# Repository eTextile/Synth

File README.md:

# eTextile-Synthesizer
### Exploring music through textile

## About the project
**eTextile-Synthesizers** are handcrafted multi-touch digital interfaces based on smart textile materials and custom electronic solutions. The project features a fully embedded multitouch controller that combines the powerful **Teensy 4.0** MCU with the **E256 eTextile matrix sensor** — a 16×16 FSR array with hardware interpolation up to 64×64 points.

The interface is configured via a **browser-based mapping application** that communicates with the device over USB-MIDI. Mappings (touchpad, slider, switch, knob, grid…) are defined visually, saved as JSON, and uploaded to the device.

### Links
* **Web page:** [synth.eTextile.org](https://synth.eTextile.org "Project web page")
* **Mapping app:** [github.com/eTextile/Mapping](https://github.com/eTextile/Mapping "Browser-based MIDI mapping application")
* **Repository:** [github.com/eTextile/Synth](https://github.com/eTextile/Synth "Project repository")
* **License:** [CC-BY-SA](https://github.com/eTextile/Synth/blob/master/LICENSE.txt "Project License")
* **Mail:** [contact@etextile.org](mailto:contact@etextile.org "eMail us")
* **Pictures:** [flickr.com](https://www.flickr.com/photos/maurin/albums/72157673740361510/ "Share your pictures with us")

## Project content
* **Hardware_textile:** eTextile-Synthesizer construction tutorial
* **Hardware_electronic:** Open Hardware electronics (KiCad)
* **Firmware:** eTextile-Synthesizer firmware (PlatformIO)
* **Software:** Demo applications (PureData, MaxMSP, Max4Live, etc.)

## Specifications
| **Feature**              | **Description**                            |
| :----------------------- | :----------------------------------------- |
| Power                    | DC 5V (USB)                                |
| Sensor resolution        | 16×16 FSRs                                 |
| Interpolated resolution  | 64×64                                      |
| Multi-touch              | User defined                               |
| Blob characteristics     | [ID, STATE, CX, CY, WIDTH, HEIGHT, DEPTH]  |
| XY resolution            | [0:127] integer                            |
| Z resolution             | [0:127] integer                            |
| FPS                      | 500–550                                    |
| Audio IN                 | ADC 16-bit (mini-jack)                     |
| Audio OUT 1              | DAC 16-bit (mini-jack)                     |
| Audio OUT 2              | Headphone (mini-jack)                      |
| Connectivity             | USB-MIDI                                   |
| Connectivity             | MIDI I/O (mini-jack)                       |
| Connectivity             | USB-MPE (TODO)                             |

## Publications
- [NIME17](http://www.nime2017.org/) - Designing a Multi-Touch eTextile for Music Performances / [Paper](https://github.com/eTextile/Matrix/blob/teensy_matrix/docs/publications/NIME17-eTextile.pdf) - [Video](https://vimeo.com/217690743)
- [MOCO17](http://moco17.movementcomputing.org/) - Music Skin: Fabric Interface for Expressive Music Control / [Paper](https://github.com/eTextile/Matrix/blob/teensy_matrix/docs/publications/MOCO17-MusicSkin.pdf)

## Copyright
Except as otherwise noted, all files in the **eTextile-Synthesizer** project folder

    Copyright (c) 2014- Maurin Donneaud

For information on usage and redistribution, and for a DISCLAIMER OF ALL WARRANTIES, see LICENSE.txt included in this folder.

## Docs
- [Video made at Schmiede 2014](http://www.kobakant.at/DIY/?p=4305/)

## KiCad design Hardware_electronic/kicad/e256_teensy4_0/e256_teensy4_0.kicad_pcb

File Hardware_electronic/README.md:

# eTextile-Synthesizer
## Exploring music through textile

### HARDWARE_ELECTRONIC

#### PCB_SCHEMATICS
Here is the last PCB schematics document : [eTextile_synth_schematics.pdf](./docs/eTextile_synth_schematics.pdf)

#### FEATURES
- Teensy 4.0 (600MHz MCU)
- eTextile-Synthesizer PCB made with **KiCad** (V5.0.*)
- Daisy chainable design using **3.5 stereo mini Jack**
    - **LINE-OUT** : High quality 16 bit DAC OUTPUT (Headphones)
    - **SIG-IN** : Audio stereo input sampling rate 44.1 kHz
    - **SIG-OUT** : High quality 16 bit DAC OUTPUT (Line)
    - **MIDI-IN** : MIDI INPUT using mini jack 
    - **MIDI-OUT** : MIDI OUTPUT using mini jack

#### BUILT_IN SWITCHES
- **Button D1 (DOT)** Short press : CALIBRATE THE SENSOR MATRIX
- **Button D1 (DOT)** Long press : SAVE CONFIG TO FLASH MEMORY (standalone mode)
- **Button D2 (STAR)** Short press : SELECT MODE (see below)
- **Button D2 (STAR)** Long press : MIDI LEARN MODE

#### SELECT MODE
    |      MODE     |       LEDs      |                     FONCTION                    |
    | :------------ | :-------------  | :---------------------------------------------- |
    | **LINE_OUT**  | D1-OFF / D2-OFF | line_out level adjustment using rotary encoder  |
    | **SIG_IN**    | D1-ON  / D2-OFF | sig_in level adjustment using rotary encoder    |
    | **SIG_OUT**   | D1-OFF / D2-ON  | sig_out level adjustment using rotary encoder   |
    | **THRESHOLD** | D1-ON  / D2-ON  | threshold value adjustment using rotary encoder |

#### MIDI LEARN
> **TODO** — not yet implemented (long press STAR is reserved for this feature).

In MIDI LEARN mode the device will send each blob parameter (X, Y, Z, width, height) one at a time so that external software can map them without ambiguity.
Use the rotary encoder to cycle through the available parameters; the currently selected parameter is the only one transmitted.
A short press on the **DOT** or **STAR** button exits MIDI LEARN mode and returns to the previous operating mode.

> **Note:** static MIDI mappings are configured via the [Mapping web app](https://etextile.github.io/Mapping/) and uploaded to the device over USB.

#### MIDI PLUG
**MIDI TRS-A (MIDI 2.0 Standard)**

#### KICAD (Prerequisite)
- Installing KiCad : https://kicad-pcb.org/
- Installing Github Libraries : https://github.com/KiCad/
```
    mkdir KiCad_Libraries
    cd KiCad_Libraries
    git clone https://github.com/KiCad/kicad-symbols
    git clone https://github.com/KiCad/kicad-footprints
    git clone https://github.com/KiCad/kicad-packages3D
```
- Configuring KiCad Libraries
```
    KiCad > Préférences > Configure path
    KICAD_SYMBOL_DIR : (add your own path) .../KiCad_Libraries/kicad-symbols
    KICAD_TEMPLATE_DIR : DO NOT CHANGE
    KICAD_USER_TEMPLATE_DIR : DO NOT CHANGE
    KIGITHUB : DO NOT CHANGE
    KISYS3DMOD : (add your own path) .../KiCad_Libraries/kicad-packages3D
    KISYSMOD : (add your own path) .../KiCad_Libraries/kicad-footprints
```
##### PCB specifications
- **Base Material** : FR-4 TG130
- **No. of Layers** : 2 layers
- **PCB Dimensions** : 70mm / 76mm
- **No. of Different Designs** : 1
- **PCB Thickness** : 1.20 mm
- **PCB Color** : Matte Black
- **Surface Finish** : ENIG
- **Minimum Solder Mask Dam** : 0.4mm
- **Copper Weight** : 1oz.
- **Minimum Drill Hole Size** : 0.3mm
- **Trace Width / Spacing** : 6/6 mil
- **Plated Half-holes / Castellated Holes** : No
- **Impedance Control** : No

##### BOM (Bill Of Materials)
```
    matrix/Hardware_electronic/kicad/e256_teensy4_0/pick_and_place/BOM_e256_teensy4_0.xls
    matrix/Hardware_electronic/kicad/e256_teensy4_0/pick_and_place/BOM_e256_teensy4_0.cvs
```

## Acknowledgements
-  Matt Venn : for his [teensy 4.0 Open-Hardware sound_card](https://github.com/mattvenn/teensy-audio-fx) made with KiCad ;-)

## TODO
- R10 470Ω → 2.2kΩ
- R15 → 4.7 kΩ
- Add hardware MIDI THRU
- Make eTextile-Synthesizer/Dasy PCB

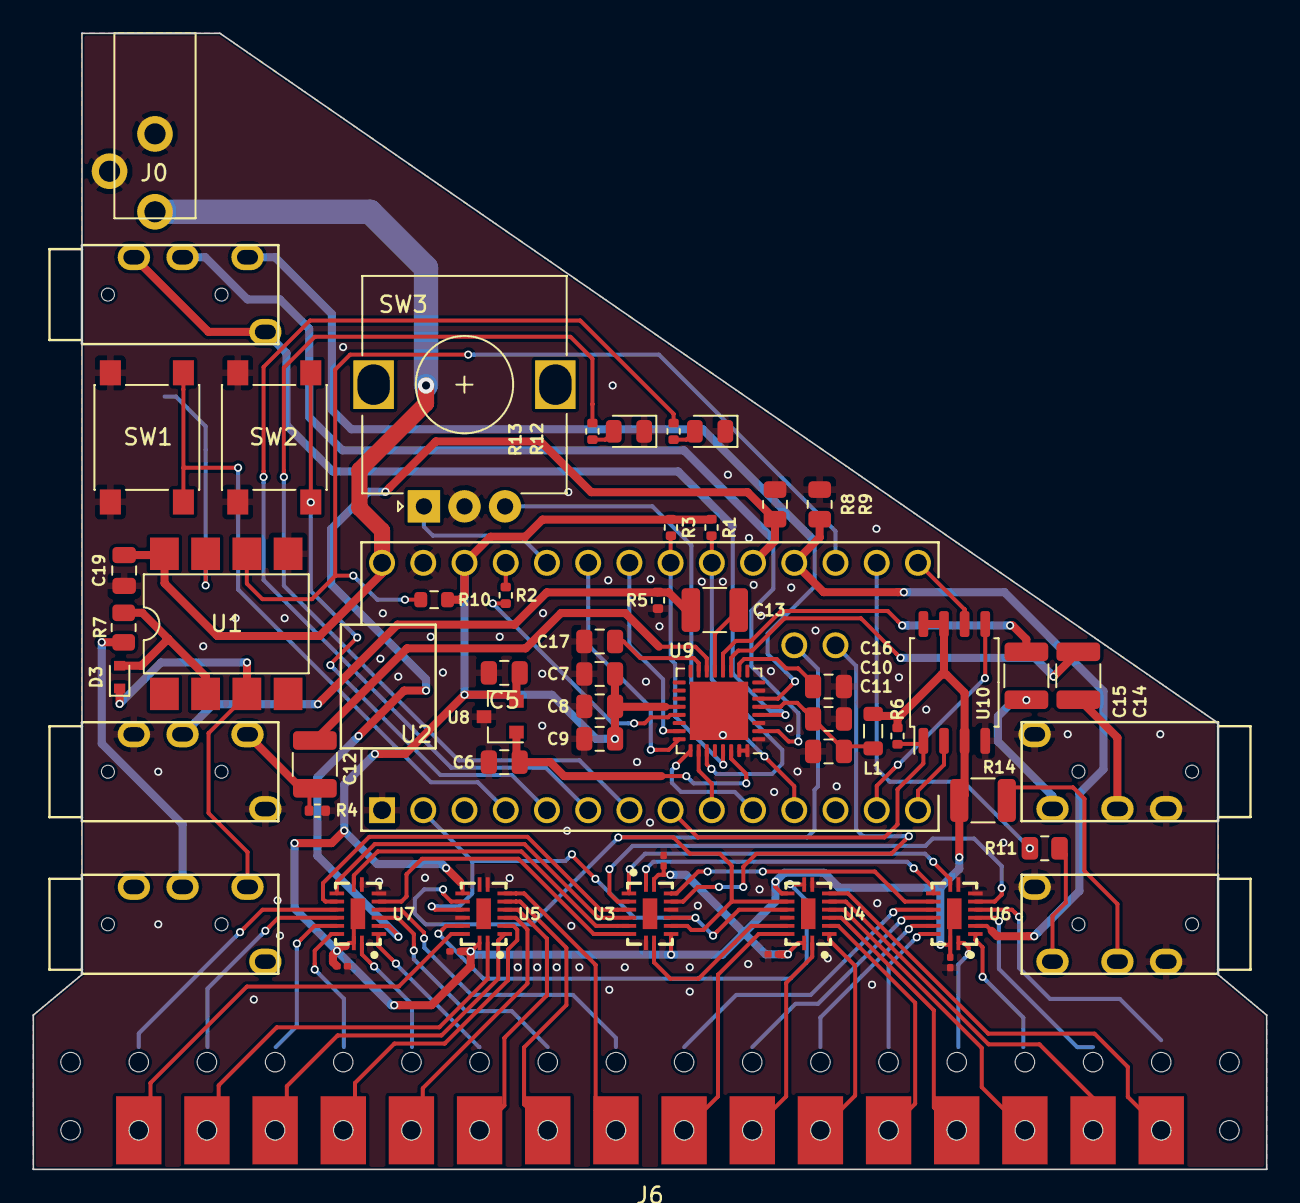
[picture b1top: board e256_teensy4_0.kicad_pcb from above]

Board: 2 copper layers, 76.0 x 70.0 mm, 58 parts (1 on the bottom side), 93 nets.

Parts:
C1, C2, C3, C4, C18: 0.1uF 6.3V X5R; C_0201_0603Metric
C5, C6: 2.2uF_X7R; C_0805_2012Metric
C7, C10: 2.2uF; C_0805_2012Metric
C8, C9, C11, C16, C17, C19: 0.1uF; C_0805_2012Metric
C12, C13, C14, C15: 1uF; C_1210_3225Metric
D1, D2: LED; LED_0805_2012Metric
D3: 1N4148; D_SOD-523
J0: Conn_Coaxial_Power; BarrelJack-SMT-DC003_Horizontal
J1: MIDI_IN; PJ-320A
J2: MIDI_OUT; PJ-320A
J3: AUDIO_IN; PJ-320A
J4: AUDIO_OUT; PJ-320A
J5: LINE_OUT; PJ-320A
J6: e256_pad_16x16; e256_pad_16X16
L1: 600R; L_0805_2012Metric
R1, R3: 2.2K; R_0402_1005Metric
R2: 100R; R_0402_1005Metric
R4, R5: 100k; R_0402_1005Metric
R6: 10K; R_0402_1005Metric
R7: 220 Ohm; R_0805_2012Metric
R8, R9: 10K; R_0805_2012Metric
R10: 470 Ohm; R_0603_1608Metric
R11: 47 Ohm 1/8W; R_0805_2012Metric
R12, R13: 100 Ohm; R_0402_1005Metric
R14: 47 Ohm 1/3W; R_1210_3225Metric
R15: 10K; R_0805_2012Metric_Pad1.20x1.40mm_HandSolder
SW1, SW2: SW_Push; SW_SPST_PTS645
SW3: RotaryEncoder_Switch; RotaryEncoder_Alps_EC12E_Vertical_H20mm
U1: 6N138SM; 6N138SM_8-SMD
U2: Teensy4.0; Teensy40
U3, U4, U5: 74HC595BQ; DHVQFN-16-2.5X3.5MM
U6, U7: 74HC4051BQ; DHVQFN-16-2.5X3.5MM
U8: MCP1811A; SOT-23
U9: SGTL5000; QFN-32-1EP_5x5mm_P0.5mm_EP3.6x3.6mm
U10: W25Q128JVS; SOIC-8_5.23x5.23mm_P1.27mm

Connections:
+1V8: C6.1, U8.1, U9.30
+5V: C19.1, J0.1, U1.8, U2.33
/SGTL5000/filter_audio_3v3: C10.1, C11.1, L1.2, U9.5
ANALOG_0: R9.1, U2.23, U6.3
ANALOG_1: R8.1, U2.24, U7.3
BCLK: U2.28, U9.24
COL_0: J6.16, U4.7
COL_1: J6.17, U4.6
COL_2: J6.18, U4.5
COL_3: J6.19, U4.4
COL_4: J6.20, U4.3
COL_5: J6.21, U4.2
COL_6: J6.22, U4.1
COL_7: J6.23, U4.15
COL_8: J6.24, U5.7
COL_9: J6.25, U5.6
COL_10: J6.26, U5.5
COL_11: J6.27, U5.4
COL_12: J6.28, U5.3
COL_13: J6.29, U5.2
COL_14: J6.30, U5.1
COL_15: J6.31, U5.15
DS_B: U3.9, U4.14
DS_C: U4.9, U5.14
ENCODER_A: SW3.A, U2.29
ENCODER_B: SW3.B, U2.11
EN_A: U3.3, U6.6
EN_B: U3.7, U7.6
GND: C1.2, C2.2, C3.2, C4.2, C5.2, C6.2, C7.2, C8.2, C9.2, C10.2, C11.2, C16.2, C17.2, C18.2, C19.2, D1.1, D2.1, J0.2, J2.R2, J2.S, J3.R2, J3.S, J4.R2, J4.S, R4.1, R5.1, R8.2, R9.2, R15.2, SW1.2, SW2.2, SW3.C, U1.5, U2.1, U2.32, U3.8, U3.13, U4.8, U4.13, U5.8, U5.13, U6.7, U6.8, U7.7, U7.8, U8.3, U9.1, U9.3, U9.7, U9.31, U9.32, U9.33, U10.4
I2C_SCL_0: R3.2, U2.26, U9.29
I2C_SDA_0: R1.2, U2.25, U9.27
I2S_IN: U2.10, U9.25
I2S_OUT: U2.9, U9.26
LED_1: R12.1, U2.6
LED_2: R13.1, U2.7
LRCLK: U2.27, U9.23
MCLK: R2.2, U2.30
MEM_CS: R6.2, U2.8, U10.1
MEM_MISO: U2.14, U10.2
MEM_MOSI: U2.13, U10.5
MEM_SCK: U2.20, U10.6
MIDI_IN: R10.2, U1.6, U2.22
MIDI_OUT: R11.2, U2.21
unnamed: C12.1, U9.14
unnamed: C12.2, J3.T, R4.2
unnamed: C13.1, U9.13
unnamed: C13.2, J3.R1, R5.2
unnamed: C14.1, U9.11
unnamed: C14.2, J4.R1
unnamed: C15.1, U9.12
unnamed: C15.2, J4.T
unnamed: C16.1, U9.10
unnamed: C17.1, U9.15
unnamed: D1.2, R13.2
unnamed: D2.2, R12.2
unnamed: D3.1, J1.T, U1.3
unnamed: D3.2, R7.1, U1.2
unnamed: J1.R1, R7.2
unnamed: J2.R1, R14.2
unnamed: J2.T, R11.1
unnamed: J5.R1, U9.2
unnamed: J5.R2, J5.S, U9.4
unnamed: J5.T, U9.6
unnamed: R2.1, U9.21
unnamed: R15.1, U1.7
ROW_0: J6.0, U6.5
ROW_1: J6.1, U6.4
ROW_2: J6.2, U6.2
ROW_3: J6.3, U6.1
ROW_4: J6.4, U6.15
ROW_5: J6.5, U6.14
ROW_6: J6.6, U6.13
ROW_7: J6.7, U6.12
ROW_8: J6.8, U7.5
ROW_9: J6.9, U7.4
ROW_10: J6.10, U7.2
ROW_11: J6.11, U7.1
ROW_12: J6.12, U7.15
ROW_13: J6.13, U7.14
ROW_14: J6.14, U7.13
ROW_15: J6.15, U7.12
S0_A: U3.15, U6.11
S0_B: U3.4, U7.11
S1_A: U3.1, U6.10
S1_B: U3.5, U7.10
S2_A: U3.2, U6.9
S2_B: U3.6, U7.9
SHIFT_OUT_CS: U2.2, U3.12, U4.12, U5.12
SHIFT_OUT_MOSI: U2.37, U3.14
SHIFT_OUT_SCK: U2.38, U3.11, U4.11, U5.11
SWITCH_A: SW1.1, U2.4
SWITCH_B: SW2.1, U2.5
VCC: C1.1, C2.1, C3.1, C4.1, C5.1, C7.1, C8.1, C9.1, C18.1, L1.1, R1.1, R3.1, R6.1, R10.1, R14.1, U2.31, U3.10, U3.16, U4.10, U4.16, U5.10, U5.16, U6.16, U6.EP, U7.16, U7.EP, U8.2, U9.20, U10.3, U10.7, U10.8

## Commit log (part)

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2021-03-21 Replaced lifo with improved multy types linked list
2021-03-23 Improved blob ID management & linked list
2021-03-29 Blobs management ZERO COPY ;-)
2021-04-01 Updated mapping gridLayout() & gridGapLayout fonction
2021-04-04 Renaming
2021-04-04 Refactoring & CleanUp
2021-04-04 FIXME: MIDI include mismatch
2021-04-04 Minor changes
2021-04-10 Midi include not wrking
2021-05-08 Refactoring thx@Nico ;-)
2021-05-08 CleanUP
2021-05-09 some more arguments removed
2021-05-10 Removed fonctions [args]
2021-05-11 MIDI include FIX
2021-05-12 Improved mapping: gridPlay() & gridGapPlay()
2021-05-14 CleanUP & refactoring notes.h
2021-05-14 Added teensy 3.2 support (in progress)
2021-05-16 Updated Teensy macro
2021-05-16 Updated comments
2021-05-16 Remove submodule
2021-05-16 Removed submodules
2021-05-16 improved interpolation
2021-05-21 Improved blob_scan() added debounce & updated mapping fonctions
2021-05-21 Minor fix
2021-05-22 BugFix gridPlay()
2021-05-31 Refactoring / quick-and-dirty commit
2021-05-31 Updated Bounce2 INSTANTIATE A Button OBJECT
2021-06-01 Refactoring DEBUGS
2021-06-01 Updated mode & lastMode management
2021-06-01 Removed unused timer
2021-06-05 Added SLIP_OSC & refactoring
2021-06-08 Updated with lastState param
2021-06-10 split transmit file & refactoring
2021-06-11 Removed fonctions params & cleanUp
2021-06-11 Polish is done
2021-06-17 Improved interp & blob
2021-06-18 Improved Velocity & polarCoord
2021-06-22 Updated mapping & midi drivers
2021-07-01 Improved polar mapping
2021-07-02 Last FIX on circular sliders mapping ;-)
2021-07-04 Updated MIDI transmit
2021-09-09 improved MIDI I/O linked list buffer
2021-09-13 Updated MIDI I/O
2021-09-13 quik
2021-09-14 Updated presets & removed forward declarations
2021-09-18 FIXED for MIDI I/O
2021-09-18 Added new MIDI protocol
2021-09-19 Added new paper & rename files
2021-09-19 fixed typos
2021-09-19 Updated TXT
2021-09-19 adding ref
2021-09-19 added ref
2021-09-19 Reorganized docs and added web file
2021-09-19 Reorganized docs and added refs folder
2021-09-19 Renamed folder
2021-09-19 Added new score
2021-09-19 added README.md
2021-09-19 Updated Pd driver
2021-09-19 added refs details
2021-09-19 updated mapping_grid_populate()
2021-09-20 Updated mapping functionality
2021-09-22 Working gridMapping() ;-)
2021-09-24 Fix doc size
2021-09-26 BUGFIX with MIDI message linked list
2021-09-27 Updated llist_save_nodes() && mapping_grid_update()
2021-09-28 BUGFIX mapping_grid_update
2021-10-02 FIX mapping_grid_populate() & mapping_grid_update()
2021-10-03 Updated with MIDI spec
2021-10-06 Added Processing & updated openFrameworks
2021-10-06 CleanUp & new median filter to test
2021-10-08 BUGFIX with MIDI communication
2021-10-09 Improved blob debouce
2021-10-10 BUGFIX blob percistent ID
2021-10-12 BUGFIX in blobID
2021-10-12 Minor FIX - IN PROGRESS
2021-10-13 Quick and dirty
2021-10-13 FUGFIX With unstable blob ID!
2021-10-13 Avoid MIDI channel 0
2021-10-13 Updated the MIDI message arguments order
2021-10-14 BUBFIX with presets[MIDI_BLOBS_LEARN].updateLed = true;
2021-10-14 BUBFIX MIDI_BLOBS_LEARN
2021-10-15 Updated MIDI messages order to keep compatibility with most software
2021-10-21 Updated MIDI callback & OSC
2021-10-21 Updated OSC
2021-10-23 Updated OSC_TRANSMIT
2021-10-23 New OSC-parser
2021-10-23 TESTING & FIX
2021-11-08 ./docs
2021-11-08 Updated for platformio
2021-11-08 Added submodules
2021-11-08 moved all .h to the include folder
2021-11-08 Trying to compile :-(
2021-11-09 Up & Running
2021-11-09 Added USB_MIDI_SERIAL
2021-11-09 Renaming constants
2021-11-11 Fixed players
2021-11-11 Adding FS
2021-11-11 Update USB_MTP_MIDI
2021-11-12 Adding USB_MTP & Json parser
2021-11-12 USB_MTP_MIDI in progress, still Linking ERROR!
2021-11-13 Update file
2021-11-14 RENAMING Fonctions & split files
2021-11-14 Removed Temp file
2021-11-15 CleanUp & renaming
2021-11-15 Fix typos, update copyright
2021-11-15 Use a custom Teensy platform variant
2021-11-15 Updated mapping_lib fonctions & some renaming
2021-11-16 arduinoJson & serialFlash FIXME!
2021-11-18 Addad mapping_lib polygon shape
2021-11-18 Updated mapping_polygon
2021-11-18 Renaming mapping_lib fonctions
2021-11-18 Added mapping_circle
2021-11-18 usb/midi: fix CPP conditional define
2021-11-18 mapping: add missing MAPPING_CSLIDER_SETUP function definition
2021-11-18 config: rework JSON config file loading
2021-11-18 Added processing.js
2021-11-18 merging_fix
2021-11-18 Fix #if defined(*)
2021-11-18 Added config mapping_circle
2021-11-19 Added all mappin_lib config presets
2021-11-19 BUGFIX in MAPPING_POLYGONS_SETUP()
2021-11-19 Updated mapping_touchpads()
2021-11-19 Updated mapping_lib
2021-11-19 Added USB_SERIAL_UPDATE_CONFIG
2021-11-19 Added Serial_upload demo code
2021-11-19 Moved USB_SERIAL_UPDATE_CONFIG() into config.json
2021-11-21 Moved preset.cpp > config.cpp
2021-11-21 Added LOAD_CONFIG & UPDATE_CONFIG mode
2021-11-22 LED control refactoring
2021-11-22 added midi_sendOut()
2021-11-23 Refactoring presets management
2021-11-23 Re-refactoring presets management
2021-11-23 refact
2021-11-24 .json uploading & loading!
2021-11-24 Fix mode management
2021-11-24 Refactoring
2021-11-25 Bug Fix
2021-11-25 BugFix
2021-11-26 Updated midiMsg & OSCmsg reading
2021-11-26 Renaming & refactoring
2021-11-26 Added ProgramChange for selecting the mode
2021-11-26 Refat update_leds();
2021-12-13 Added MIDI sysex to load config via MIDI & refactoring
2021-12-14 Removed OSC & MTP & Added ERROR codes
2021-12-14 fix config file name
2021-12-14 configData & configDataLength declared as global :-(
2021-12-16 Fix MIDI input handler
2021-12-23 Added allocate() for config file memmory allocation
2021-12-25 Working state
2021-12-26 Minor swing
2022-01-03 BUGFIX with LEDs modes&levels
2022-01-06 Updated args of setup_leds() & set_level()
2022-01-06 Updated date to 2014-2022
2022-01-06 Updated args of read_encoder() & fade_leds() & blink_leds()
2022-01-08 increase MAX_BLOBS FIX Bug & cleanUp
2022-01-09 Removed BLOB_LEARN MODE it will be done with the MAPPING_MODE
2022-01-11 Updated MIDI Manufacturer ID to 7D
2022-01-15 first attempt to parse MIDI CONFIG
2022-01-16 LOAD_MODE FIXED
2022-01-16 In progress
2022-01-17 MIDI SYSEX loading is working
2022-01-17 Testing
2022-01-17 Testing done
2022-01-17 Added realloc()
2022-01-18 Updated MODES & LEVELS & added STATES (SOC)
2022-02-18 upToDate with Mapping-app
2022-02-19 Updated point_t & added vertrice_t
2022-02-22 Updated e256_calibrate()
2022-03-16 Cleaning MODES
2022-03-17 modes renaming & cleanUP
2022-03-17 FIX Loading Mode & updated MODES
2022-03-18 FIX Upload CONF
2022-03-29 Added SYNC_MODE
2022-04-12 Updated low level MIDI_CHANNELS...
2022-04-12 Updated low level MODES
2022-04-12 Updated boot MODES
2022-04-14 #define PENDING_MODE_TIMEOUT 2000
2022-04-15 Updated SYNC & CONFIG_FILE
2022-04-30 Updated flash & load config
2022-05-03 Added Get config
2022-05-05 Minor chages
2022-05-07 Separated load_config() and applay_config()
2022-05-27 Upated Json parsing
2022-05-30 Added new line at end of files
2022-06-02 Add installation steps to build and flash the firmware
2022-06-26 Renaming functions & updated hSlider & vSlider --> generic slider (H&V)
2022-11-14 parameters adjustment to work with the mapping lib app
2023-03-31 CleanUP & Updated mapping_lib
2023-04-01 removed gitmodules
2025-02-23 HELP with llist_builder()
2025-02-24 Tmp FIX
2025-02-26 llist_builder() bugfix attempt
2025-02-26 llist: improve & fix
    * Add llist_alloc_node & llist_free_node
    * Fix llist_pop_node_front not returning head node, but next one
    * Fix llist_pop_front recycling NULL nodes to the pool
    * Fix llist_push_front & llist_push_back not checking when pool is
    exhausted
2025-03-01 FIX sysEx_chunks computation
2025-03-01 matrix_find_blobs(); TESTING
2025-03-01 FIX DEAD BLOBS REMOVER
2025-03-01 tweaking
2025-03-01 Renaming mapping_data_ptr -> touch_ptr
2025-03-04 Added multitouch
2025-03-04 added some specs
2025-03-14 FIX: Added pressure limit to 127 for MIDI transmit
2025-03-17 In progress / the midi_out is not working!
2025-03-22 MIDI out is now working with the new linked linst
2025-03-24 Added new blob status management && CleanUp
2025-03-25 Added start play stop to each GUI
2025-03-28 Updated midi start() play() stop()
2025-03-28 Removed threshold value subtract
2025-03-28 added get_type_name(MidiType code) for debug
2025-03-28 Changed Z_MAX value 255 -> 127
2025-03-28 Comment midi noteOff when release
2025-03-28 Uncomment midi start() play() stop()
2025-03-28 Added: send midi msg only if midi value is changing
2025-03-29 DEBUGED some func in mapp_switch & mapp_slider
2025-03-31 BUG FIX in mapping.cpp : Constraint added to avoid blob and mapping association if the mapping does not accept more than the maximum number of blobs defined in the config
2025-03-31 BUG FIX in mapping.cpp : refact
2025-04-01 Renaming play_func -> continue_func
2025-04-05 Refact & CleanUp
2025-04-05 Renaming play() -> continue()
2025-04-07 BUGFIX with blob status
2025-04-07 Changed mapping_alloc func void -> bool
2025-04-08 BUGFIX with blob_cout++ placed at wrong position
2025-04-09 Added TODO
2025-04-09 Added RELEASED_IN & [200~n_RELEASED_IN~
2025-04-17 Updated blob detection
2025-04-25 Added THROUGH_MODE & CleanUp
2025-04-29 mapping_lib Update nead TESTING
2025-04-30 Comment Serial.printf
2025-05-11 Refact touch_1d_s touch_2d_s touch_3d_s & all the shirt
2025-05-11 FIX usb_read_pitch_bend()
2025-05-13 updated module
2025-05-13 cleanUp setups
2025-05-20 Flip X origin
2025-05-20 Flip Y axis
2025-06-03 ERROR with includes
2025-06-06 BUG FIX with the include
2025-12-25 BUGFIX with switch parmas
2025-12-29 BUGFIX with MIDI params
2026-04-23 BUGFIX MIDI filter: last_val now updated only on send, add mapp_grid
2026-04-23 Fix typos: recive->receive, incomming->incoming, rescure->rescue, toucpad->touchpad
2026-04-24 Add move_t/populate_t types, MAX_SLIDER_STEPS and slider struct fields
2026-04-24 Slider: implement ROL step mode, all populate modes and config parsing
2026-04-24 Update README: document slider step and populate modes
2026-04-25 Slider: fix NoteOff via llist_push_front, avoid stack-allocated midi_msg_t
2026-04-25 Add MATRIX_INTERP_MODE and MATRIX_INTERP_MODE_DONE enum values
2026-04-25 MATRIX_INTERP_MODE: chunked SysEx transmission and loop case
2026-04-25 Handle CC on MIDI_LEVELS_CHANNEL to set firmware levels from host
2026-04-26 README: update for PlatformIO, mapping app, MPE, interpolated resolution
2026-04-26 docs: fix image, PlatformIO, HTML structure, copyright, GitHub link
2026-04-26 docs: use static Flickr URL for mapping toolkit image
